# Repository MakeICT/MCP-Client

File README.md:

# MCP-Client
Clients for the Master Control Program

Code compiled using ESP-IDF v3.3. Installation instructions can be found here: https://docs.espressif.com/projects/esp-idf/en/stable/get-started/index.html#introduction

#test commit

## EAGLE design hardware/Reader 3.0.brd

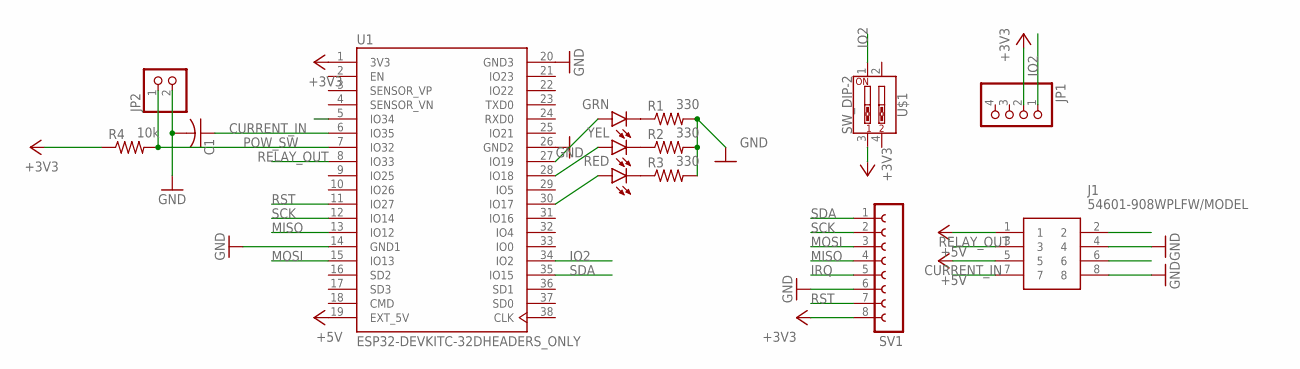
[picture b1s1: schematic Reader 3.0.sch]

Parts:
C1: C-US025-025X050; C025-025X050
GRN: LED5MM
J1: 54601-908WPLFW/MODEL; HDRV4W64P254_1X4_1016X508X838B
JP1: PINHD-1X4/90; 1X04/90
JP2: PINHD-1X2/90; 1X02/90
R1, R2, R3: 330; 0204/7
R4: 10k; 0204/7
RED: LED5MM
SV1: FE08-1; HDR_F_1X8
U1: ESP32-DEVKITC-32DHEADERS_ONLY; ESP32_DEVKITC_DIP
U$1: SW_DIP-2
YEL: LED5MM

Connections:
+3V3: JP1.2, R4.1, SV1.8, U1.1 (3V3), U$1.3
+5V: J1.1, J1.5, U1.19 (EXT_5V)
CURRENT_IN: C1.1, J1.7, U1.6 (IO35)
GND: C1.2, J1.4, J1.8, JP2.2, R1.2, R2.2, R3.2, SV1.6, U1.14 (GND1), U1.20 (GND3), U1.26 (GND2)
IO2: JP1.1, U1.34 (IO2), U$1.1
IRQ: SV1.5
MISO: SV1.4, U1.13 (IO12)
MOSI: SV1.3, U1.15 (IO13)
unnamed: RED.A, U1.30 (IO17)
unnamed: U1.28 (IO18), YEL.A
unnamed: GRN.A, U1.27 (IO19)
unnamed: GRN.K (C), R1.1
unnamed: R2.1, YEL.K (C)
unnamed: R3.1, RED.K (C)
POW_SW: JP2.1, R4.2, U1.7 (IO32)
RELAY_OUT: J1.3, U1.8 (IO33)
RST: SV1.7, U1.11 (IO27)
SCK: SV1.2, U1.12 (IO14)
SDA: SV1.1, U1.35 (IO15)

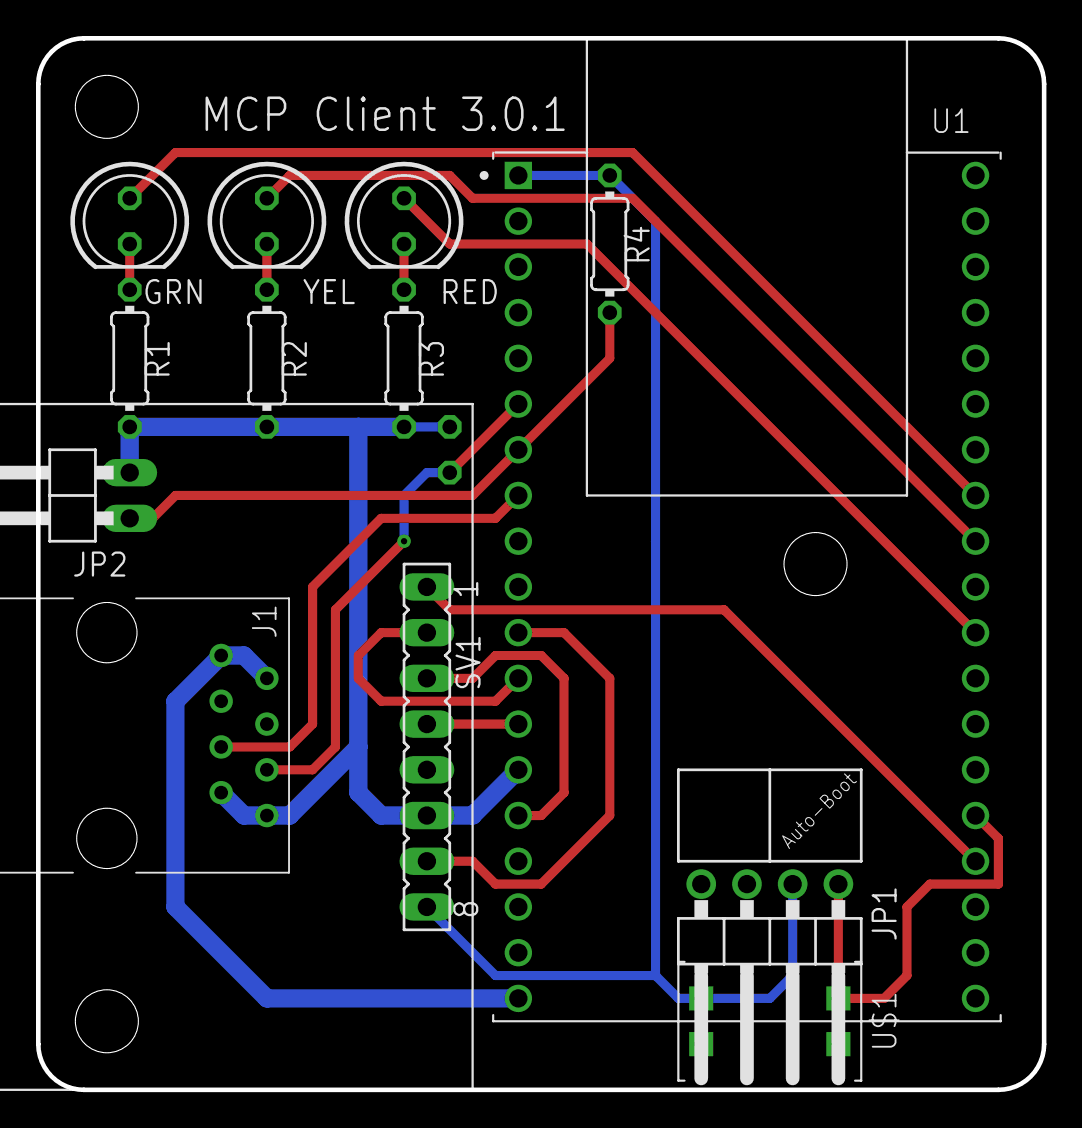
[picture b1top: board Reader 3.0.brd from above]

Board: 2 copper layers, 55.9 x 58.4 mm, 14 parts (1 on the bottom side), 18 nets.

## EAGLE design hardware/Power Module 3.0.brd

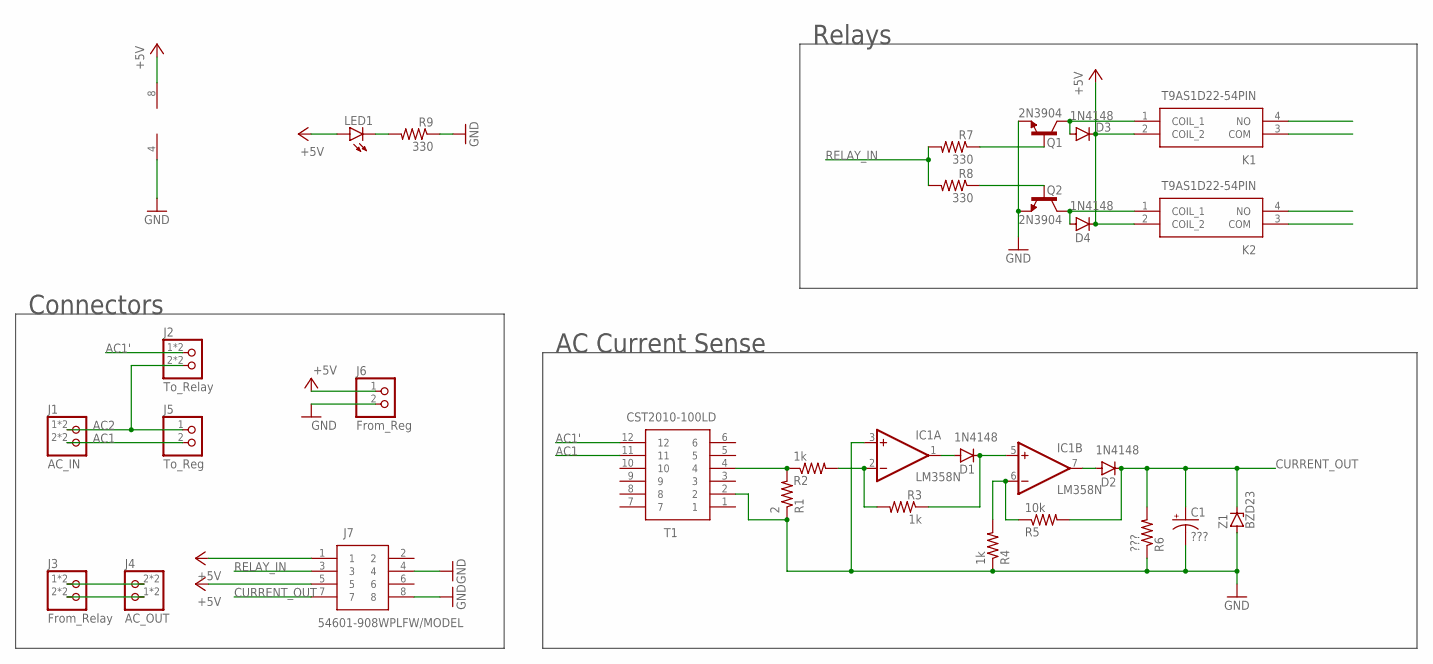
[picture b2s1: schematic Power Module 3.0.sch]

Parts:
C1: ???; E1,8-4
D1, D2, D3, D4: 1N4148; DO35-7
IC1: LM358N; DIL08
J1: AC_IN; HDRRA4W64P762_2X2_1016X254X556B
J2: To_Relay; HDRRA4W64P762_2X2_1016X254X556B
J3: From_Relay; HDRRA4W64P762_2X2_1016X254X556B
J4: AC_OUT; HDRRA4W64P762_2X2_1016X254X556B
J5: To_Reg; HDRV2W64P792_1X2_1016X508X838B
J6: From_Reg; HDRV2W165P396_1X2_1016X508X838B
J7: 54601-908WPLFW/MODEL; HDRV4W64P254_1X4_1016X508X838B
K1, K2: T9AS1D22-54PIN; T9AS5D1212313932103-2
LED1: LED5MM
Q1, Q2: 2N3904; TO92
R1: 2; 0204/7
R2, R3, R4: 1k; 0204/7
R5: 10k; 0204/7
R6: ???; 0204/7
R7, R8, R9: 330; 0204/7
T1: CST2010-100LD; CST2010100LD
Z1: BZD23; SOD81

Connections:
+5V: D3.C, D4.C, IC1.8 (V+), J6.1, J7.1, J7.5, K1.2 (COIL_2), K2.2 (COIL_2), LED1.A
AC1: J1.2, J1.3 (2), J5.2, T1.11
AC1': J2.1, J2.4 (1), T1.12
AC2: J1.1, J1.4 (1), J2.2, J2.3 (2), J5.1
CURRENT_OUT: C1.+, D2.C, J7.7, R5.2, R6.2, Z1.C
GND: C1.-, IC1.3 (+IN), IC1.4 (V-), J6.2, J7.4, J7.8, Q1.3 (E), Q2.3 (E), R1.1, R4.1, R6.1, R9.1, T1.2, Z1.A
unnamed: J3.1, J3.4 (1), J4.2, J4.3 (2)
unnamed: R1.2, R2.1, T1.4
unnamed: D1.A, IC1.1 (OUT)
unnamed: J3.2, J3.3 (2), J4.1, J4.4 (1)
unnamed: D1.C, IC1.5 (+IN), R3.1
unnamed: IC1.6 (-IN), R4.2, R5.1
unnamed: IC1.2 (-IN), R2.2, R3.2
unnamed: D3.A, K1.1 (COIL_1), Q1.1 (C)
unnamed: D2.A, IC1.7 (OUT)
unnamed: D4.A, K2.1 (COIL_1), Q2.1 (C)
unnamed: Q1.2 (B), R7.1
unnamed: Q2.2 (B), R8.1
unnamed: LED1.K (C), R9.2
RELAY_IN: J7.3, R7.2, R8.2

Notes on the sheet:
AC Current Sense
Relays
Connectors

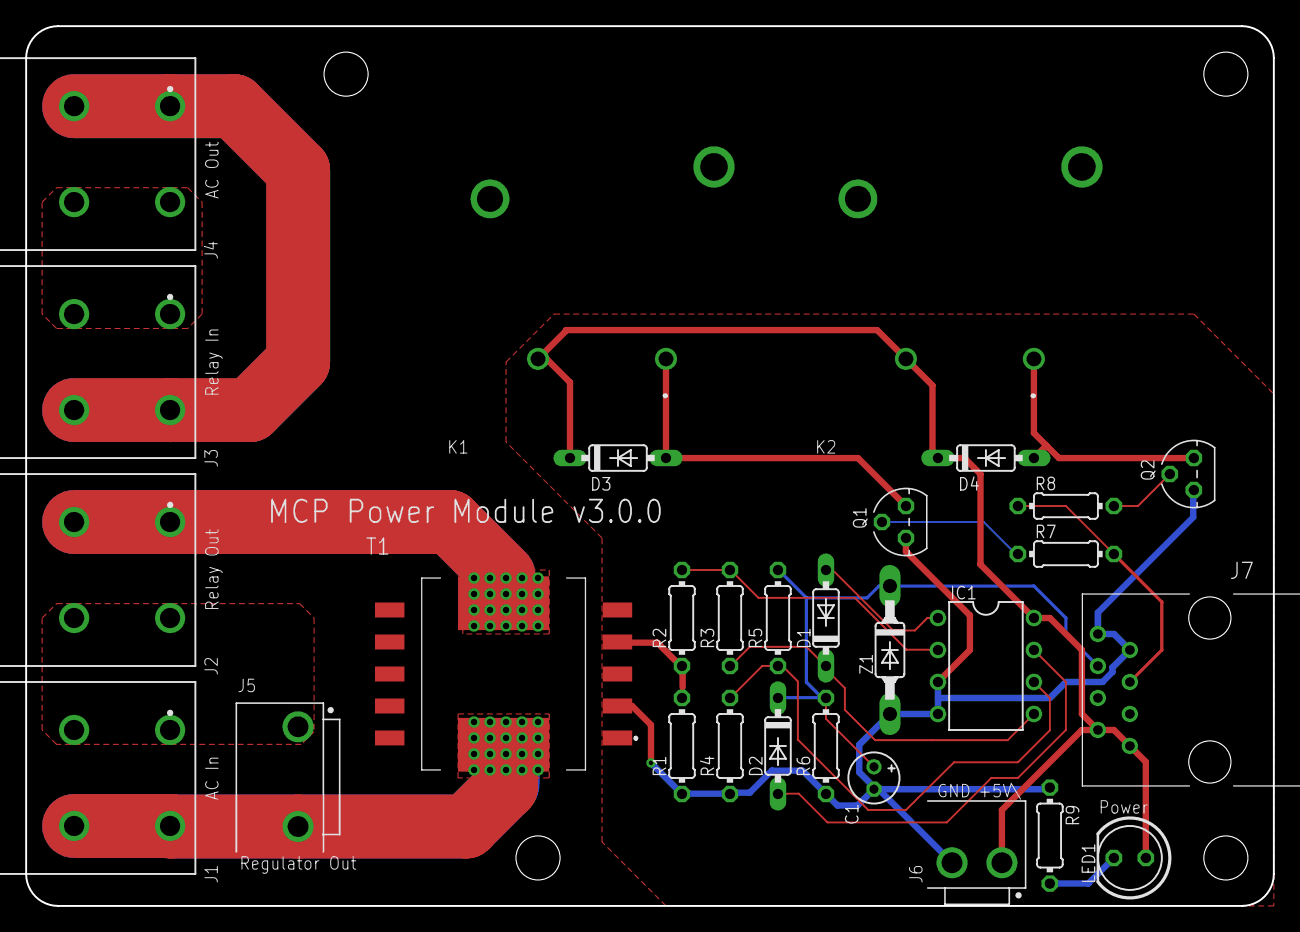
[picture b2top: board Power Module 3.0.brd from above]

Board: 2 copper layers, 99.1 x 69.8 mm, 29 parts (0 on the bottom side), 20 nets.

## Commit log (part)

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2015-09-01 restructure
2015-10-08 Add Tom's 9-2015 schematic
2015-10-08 Add Tom's 13-2015 schematic
2015-10-10 Update from 9-2015
2015-10-27 Add initial firmware -test code in place for: >LCD >NFC Reader >Max485 >NeoPixel Ring
2015-11-10 Work on rs485 communication code >add function to format packet >add python test code for pi
2015-11-11 Fix bug rs485 module bug, delete workaround code
2015-11-12 Reduce excess code -remove old test code -fix minor serial bug -clean up some formatting
2015-11-12 Add code to process incoming packets
2015-11-13 add different patterns for neopixel ring -solid, flash, pulse, and chase modes -reduced frequency of NFC scans to smooth animation
2015-11-15 Add audio, increase code efficiency -eliminate unnecessary NeoPixel updates -clean up some unused code and libraries
2015-11-15 Fix index rollover causing audio to repeat
2015-11-17 Re-organize code -add function to send button / door states -add class for door strike -re-arrange serial code
2015-11-20 Add code to support Hardware Serial for RS485
2015-11-23 Remove SoftwareSerial dependency - move to hardware serial port - fix error in byte stuffing algorithm - modify serial test code
2015-11-24 fix minor serial debug bug
2015-11-24 Modify audio code, fix serial bugs -restructure audio to take byte arrays -tunes can now be sent over network -bug preventing serial rx fixed
2015-12-28 add python debug cli
2016-01-10 Modify serial code for master-slave operation. WIP.
2016-01-10 More serial changes
2016-01-24 Update test cli to work with new serial protocol
2016-01-24 Huge re-write of serial code -change packet format -update internal packet handling
2016-01-25 Re-write debug output code -add different log levels -generalize macro across all files -re-write log messages
2016-01-25 Clean up code -delete duplicate/useless sections -reduce spaghetti code -add dump log level -add more logs
2016-01-25 Fix serial bugs -packets were found invalid due to incorrectly pulling (fake) crc from packet -fixed sending NAK on packets not addressed to device -added more logging
2016-01-27 Fix failure to go into WAIT_SEND after reading an NFC card
2016-01-27 Improve handling of serial data
2016-02-17 Add debugging to various files, fix bug in CRC calculation for escaped packets
2016-03-02 Fix crash caused by verifying CRC
2016-03-09 Add handling of deny message, fix minor logging bugs
2016-03-09 Add resend on timeout and associated logging
2016-03-23 add missing break statement
2016-03-26 Immediately relatch when door opens
2016-03-26 fix bug sending UIDs of less than 7 bytes
2016-03-30 Add code to write LCD from serial command
2016-03-30 Modify serial protocal flags
2016-04-02 Detect NFC reader failures, improve logging
2016-04-03 Improve light code
2016-04-06 Door unlock now takes 2 byte time; increased max unlock duration
2016-05-01 fix serial boo-boos - don't wait for response on ACKs and resend the last non-ACK packet. Oops. - properly increment transaction ID when sending new packets
2016-05-04 Add door bell, make address assignable
2016-05-12 Fix serial issues, add conditionals for different modules -fix transaction ID not incrementing properly on received packets -improve collision detection and avoidance
2016-07-07 Fix same ID resend timeout
2016-07-14 Fix client handling of broadcast packets
2016-07-16 Add makefile for driver source, restructure source and libs
2016-07-16 Add serial message on client start
2016-07-17 Move module configuration to makefile
2016-07-18 Add first run detection
2016-07-18 Add setting address to default on first run
2016-07-19 Fix handling of client address initialization
2016-07-20 Implement detection of server disconnect
2016-07-21 Minor formatting changes
2016-07-21 Move files back for Arduino IDE compatibility :(
2016-07-23 Eagle PC board files and mill files
    Current board files as of July 2016 Tom
2016-07-23 Fix failure to use correct client address in response packets.
2016-07-27 Add watchdog timer to prevent client freezes
2016-07-29 Add hard reset for NFC reader after 2 failed attempts to restart it -also initialize some variable and clean some formatting
2016-07-29 Add forced reset if reader cannot be recovered
2016-08-01 Modify config command processing
2016-08-01 Tweak reader reset code
2016-08-01 Improve reader failure reset logic
2016-08-03 expand configuration saving/loading, add structs for tunes and lights
2016-08-03 Finish config improvements, add handling for configuration over serial
2016-08-03 Clean up some config errors, use EEPROM config for lights and sounds
2016-08-03 Fix config save/load error, add configs for wait and error lights
2016-08-04 remove unused code, trim some debug output
2016-08-04 re-add mistakenly removed light sequence when unlocking
2016-08-04 Move board milling files to proper folder
2016-08-04 Remove unnecessary struct and function from config class
2016-08-07 Re-arrange reader code
2016-08-24 tweak NFC read error detection
2016-08-30 Add doorbell support on client and server
2016-09-06 Brian is whining about the grainy audio.
2016-09-06 Update config version
2016-12-07 change pin assignments
2017-01-01 make latch work when no door switch is present
2017-01-08 Fix missing return value in reader initialization. oops.
2017-01-11 minor code clean-up -resolve warnings -re-configure some pre-processor directives in reader.cpp
2017-01-16 update .gitignore, add new board files, put gcode files in new folder
2017-01-19 New client board V0.1
2017-01-31 Move pin definitions to definitions.h, fix doorbell input declaration
2017-02-01 Redefine pnis for new board layout
2017-02-01 modify platformio.ini for new board layout
2017-02-07 initial addition of ili9340 code
2017-02-07 Fix DRC errors in wifi client board.
2017-02-08 re-assign pins for original board layout
2017-02-08 actually revert pin assignments and clock speed this time
2017-02-08 fix pin name
2017-02-08 remove ili9340 code
2017-02-26 fix wdt boot loop
2018-08-10 Add files for esp32 client
2018-08-16 Add base code for mfrc522 reader, refactor for cpp compatibility
2018-08-16 add api calls to get user info by nfcID and write logs
2018-08-16 re-arrange http calls, add led class, start adding json parser
2018-08-17 add mor missing dependencies
2018-08-17 add more missing dependencies
2018-08-17 fix logging function
2018-08-19 add keepalive modify light display.
2018-08-20 fix bug in fetching HTTP responses
2018-08-21 re-arrange json parsing and check_card functions
2019-02-19 add power switch, bring function in line with current raspberry pi based client w
2019-02-19 update gitignore
2019-03-05 add new eagle project filesy
2019-03-05 add rj45 jack to board
2019-03-05 Assign jack pins
2019-03-05 change unlock pin
2019-03-05 add api function for checking group enrollment
2019-03-05 re-order the power off sequence so green light doesn't stay on if network is slow
2019-03-12 Slight adjustments to board layout, add pullup resistor
2019-03-12 remove old files
2019-03-15 begin ws2812 support
2019-03-20 switch red and green LED pins in software
2019-03-20 change LED names in circuit layout
2019-04-06 add gitignore for eagle backups
2019-04-06 Add first draft of power module 3.0.0
2019-04-06 Replace LM324 with LM358, clean up component names, silkscreen layout, and some routing
2019-04-06 add power indication led to relay module
2019-04-07 fix VH connectors on relay module
2019-04-13 Minor Power Module layout tweaks, rename files
2019-04-19 add current detection shutoff
2019-04-20 fix current input wiring * ADC2 on IO25 is not usable when WiFi is active. * switch to ADC1 on IO32 * add capacitor to input * remove pullup resistor
2019-05-04 add config settings for client tag and current timeout
2019-06-02 add submodule for ws2812
2019-06-02 add test code for ws2812
2019-06-02 add TFT library
2019-07-24 re-authenticate if API call fails
2020-04-08 remove JSON parsing code from main file
2020-04-08 comment out some API calls that don't currently apply to the new library
2020-04-08 use new API call for checking NFC ID
2020-04-08 add output for disarming alarm
2020-07-31 toms changes
2020-08-12 Update README.md
    Test commit to verify permissions.
2020-08-17 restored ignore file to not track build folder and configs
2020-08-17 removing build folder
2020-12-07 remove CMakeLists from tracking
2020-12-07 add partition table
2020-12-07 comment out references to server root cert
2020-12-07 remove unused files
2020-12-07 add binary tree search and code for saving/loading badges in NVS
2020-12-07 make client_id configurable
2020-12-07 modify logging output
2020-12-07 pin definitions for new hardware
2020-12-07 add GPIO interrupt handling for inputs
2020-12-07 add error response to http_api_task
2020-12-07 whitespace formatting
2020-12-07 add api call for retrieving list of allowed keycards
2020-12-07 attempt to re-connect if wifi is lost
2020-12-07 add LED handler task
2020-12-07 init functions
2020-12-07 change SPI pin numbers
2020-12-07 track MFRC522Debug.cpp
2020-12-07 update and fix some includes
2020-12-07 remove extra header file
2020-12-07 fix regression bugs
2020-12-07 remove example partition file
2021-01-14 audio and rgb led changes
2021-01-15 return int response from authenticate_nfc instead of bool
2021-01-15 add retry in check_card function
2021-01-15 add simple audio support
2021-01-15 update alarm arm/disarm process
2021-01-15 move new library files to correct folder
2021-01-15 fix incorrect partition file name
2021-01-17 update platformio.ini to work with the current hardware
2021-01-18 add 3 second delay after card rejection
2021-01-18 wait for wifi connection before starting main loop
2021-01-18 temp disable audio output until it can be fixed to not delay door unlock
2021-01-18 don't show door unlock lights if door does not unlock due to alarm
2021-01-18 disable wifi power saving to prevent GPIO 36 and 39 from constantly creating interrupts remove gpio handler loop delay
2021-04-03 move network code to separate files, add ethernet support
2021-04-07 rename mcp_api_new.h to mcp_api.h
2021-04-07 update API code - better failure handling - ability to handle chunked responses - ability to specify HTTP method
2021-04-07 remove check_card() function - retries are now handled in the API code
2021-04-08 split mcp_api into .h and .cpp files, clean up includes
2021-04-08 remove ethernet reset pin assignment
2021-04-08 move LED handling to separate files and wrap it in a new class
2021-04-08 re-organize some variables, remove more useless code
2021-04-08 immediately write LED state on pattern change, don't write when unchanged
2021-04-09 change log tag declarations to get rid of compiler warnings
2021-04-09 remove unused #includes
2021-04-09 remove unused menu configurations
2021-04-09 reduce WiFi connect failure sleep time from 5 minutes to 5 seconds
2021-04-09 update main file header comment
2021-04-09 add states for active alarm and network disconnection
2021-04-09 minor cleanup
2021-04-10 add websocket support, create MCPLink class to handle server communication
2021-04-10 add function for setting state, add state for no server connection
2021-04-10 fix bug that caused only first and last states added to a light pattern to display
2021-04-10 remove a couple unused constants
2021-04-10 fix a couple of light-related bugs
2021-10-24 add OOM restart
2021-10-27 improve memory management and logging in websocket
2021-10-27 add (probably unnecessary) heartbeat task
2021-10-27 add websocket reconnect
2021-10-28 remove hard-coded test values
2021-10-28 add heartbeat task stack highwater mark tracking
2021-10-28 tweak reject light pattern
2021-10-28 rename menuconfig entry
2021-11-01 fix crash when trying to activate WiFi power saving while using ethernet
2021-11-01 fix LEDs not flashing on system start
2021-11-01 set hostname based on configured client ID
2021-11-02 remove unused secondary server config
2021-11-02 add option to set static IP address
2021-11-02 update deprecated network and event functions
